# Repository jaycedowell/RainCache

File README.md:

# RainCache

## Parts List
 * Arduino Nano ESP32
 * Adafruit Universal USB / DC / Solar Lithium Ion/Polymer charger - bq24074
 * Adafruit MAX17048 LiPoly / LiIon Fuel Gauge and Battery Monitor
 * Adafruit VL53L1X Time of Flight Distance Sensor - ~30 to 4000mm
 * Xain-USA: 3.7V 4400mAh, Li-ion rechargeable Battery Pack
 * Solar panel charger, 3W 6V
 * Norwesco 44405 1175 gallon Low Profile Underground Water Tank - x4
 * 3" PVC cap
 * 3" to 1 1/2" PVC reducer

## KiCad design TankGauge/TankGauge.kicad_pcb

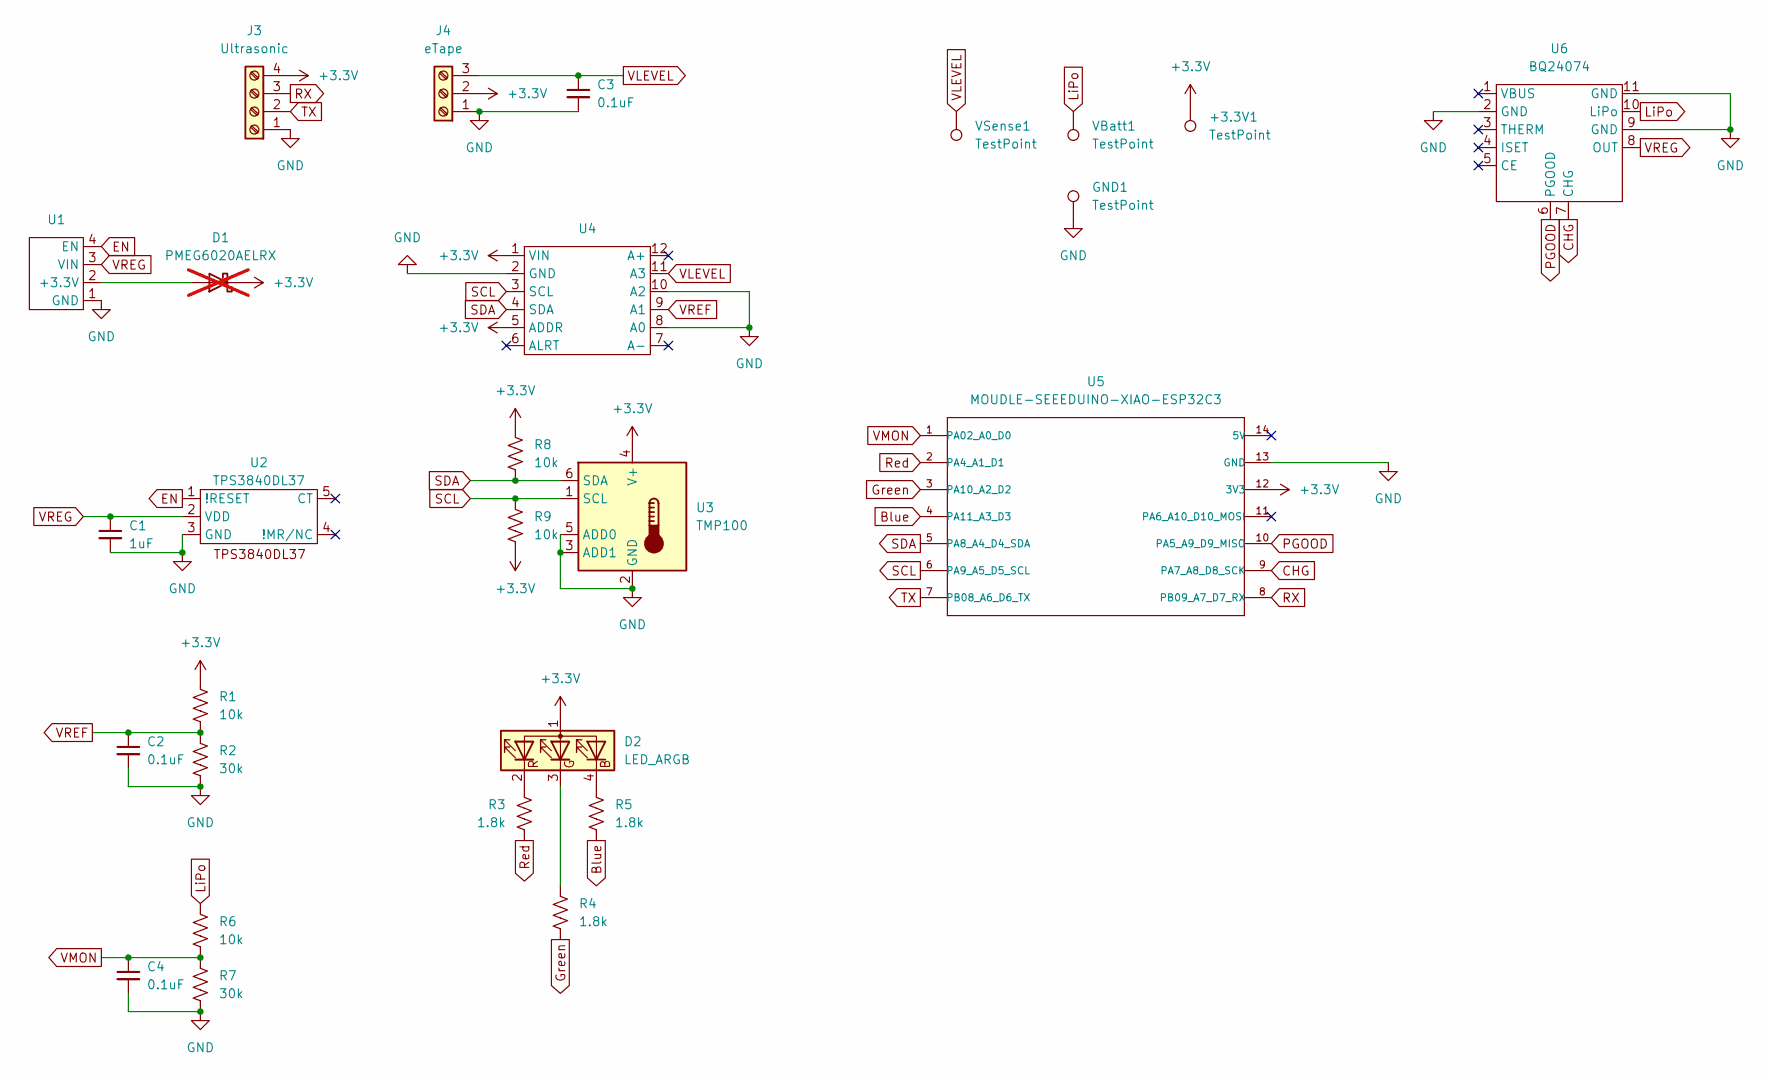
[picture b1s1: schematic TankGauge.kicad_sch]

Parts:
+3.3V1: TestPoint; TestPoint_Pad_D2.0mm
C1: 1uF; C_0805_2012Metric_Pad1.18x1.45mm_HandSolder
C2, C3, C4: 0.1uF; C_0805_2012Metric_Pad1.18x1.45mm_HandSolder
D1: PMEG6020AELRX; Nexperia_CFP3_SOD-123W; not fitted
D2: LED_ARGB; LED_Kingbright_AAA3528ESGCT
GND1: TestPoint; TestPoint_Pad_D2.0mm
J3: Ultrasonic; PinHeader_1x04_P2.54mm_Vertical
J4: eTape; PinHeader_1x03_P2.54mm_Vertical
R1, R6, R8, R9: 10k; R_0805_2012Metric_Pad1.20x1.40mm_HandSolder
R2, R7: 30k; R_0805_2012Metric_Pad1.20x1.40mm_HandSolder
R3, R4, R5: 1.8k; R_0805_2012Metric_Pad1.20x1.40mm_HandSolder
U1: TLV62569; TLV62569 Breakout Board
U2: TPS3840DL37; SOT-23-5_HandSoldering
U3: TMP100; SOT-23-6
U4: ADS1115 Breakout Board
U5: MOUDLE-SEEEDUINO-XIAO-ESP32C3; XIAO-ESP32C3
U6: BQ24074; PinHeader_1x11_P2.54mm_Vertical
VBatt1: TestPoint; TestPoint_Pad_D2.0mm
VSense1: TestPoint; TestPoint_Pad_D2.0mm

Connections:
+3.3V: +3.3V1.1, D1.1 (K), D2.1 (A), J3.4, J4.2, R1.1, R8.1, R9.2, U3.4 (V+), U4.1 (VIN), U4.5 (ADDR), U5.12 (3V3)
Blue: R5.2, U5.4 (PA11_A3_D3)
CHG: U5.9 (PA7_A8_D8_SCK), U6.7 (CHG)
EN: U1.4 (EN), U2.1 (!RESET)
GND: C1.2, C2.2, C3.2, C4.2, GND1.1, J3.1, J4.1, R2.2, R7.2, U1.1 (GND), U2.3 (GND), U3.2 (GND), U3.3 (ADD1), U3.5 (ADD0), U4.2 (GND), U4.8 (A0), U4.10 (A2), U5.13 (GND), U6.2 (GND), U6.9 (GND), U6.11 (GND)
Green: R4.2, U5.3 (PA10_A2_D2)
LiPo: R6.1, U6.10 (LiPo), VBatt1.1
unnamed: D1.2 (A), U1.2 (+3.3V)
unnamed: D2.4 (BK), R5.1
unnamed: D2.3 (GK), R4.1
unnamed: D2.2 (RK), R3.1
PGOOD: U5.10 (PA5_A9_D9_MISO), U6.6 (PGOOD)
RX: J3.3, U5.8 (PB09_A7_D7_RX)
Red: R3.2, U5.2 (PA4_A1_D1)
SCL: R9.1, U3.1 (SCL), U4.3 (SCL), U5.6 (PA9_A5_D5_SCL)
SDA: R8.2, U3.6 (SDA), U4.4 (SDA), U5.5 (PA8_A4_D4_SDA)
TX: J3.2, U5.7 (PB08_A6_D6_TX)
VLEVEL: C3.1, J4.3, U4.11 (A3), VSense1.1
VMON: C4.1, R6.2, R7.1, U5.1 (PA02_A0_D0)
VREF: C2.1, R1.2, R2.1, U4.9 (A1)
VREG: C1.1, U1.3 (VIN), U2.2 (VDD), U6.8 (OUT)

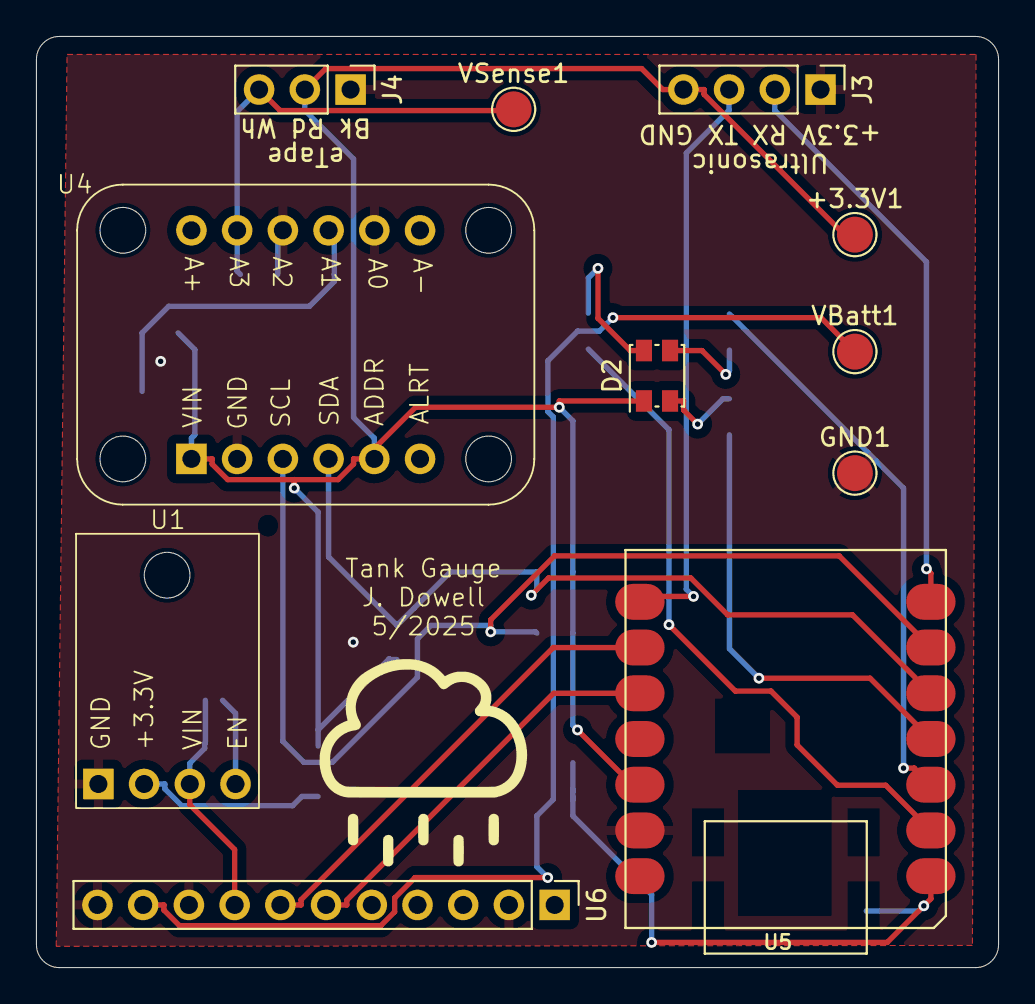
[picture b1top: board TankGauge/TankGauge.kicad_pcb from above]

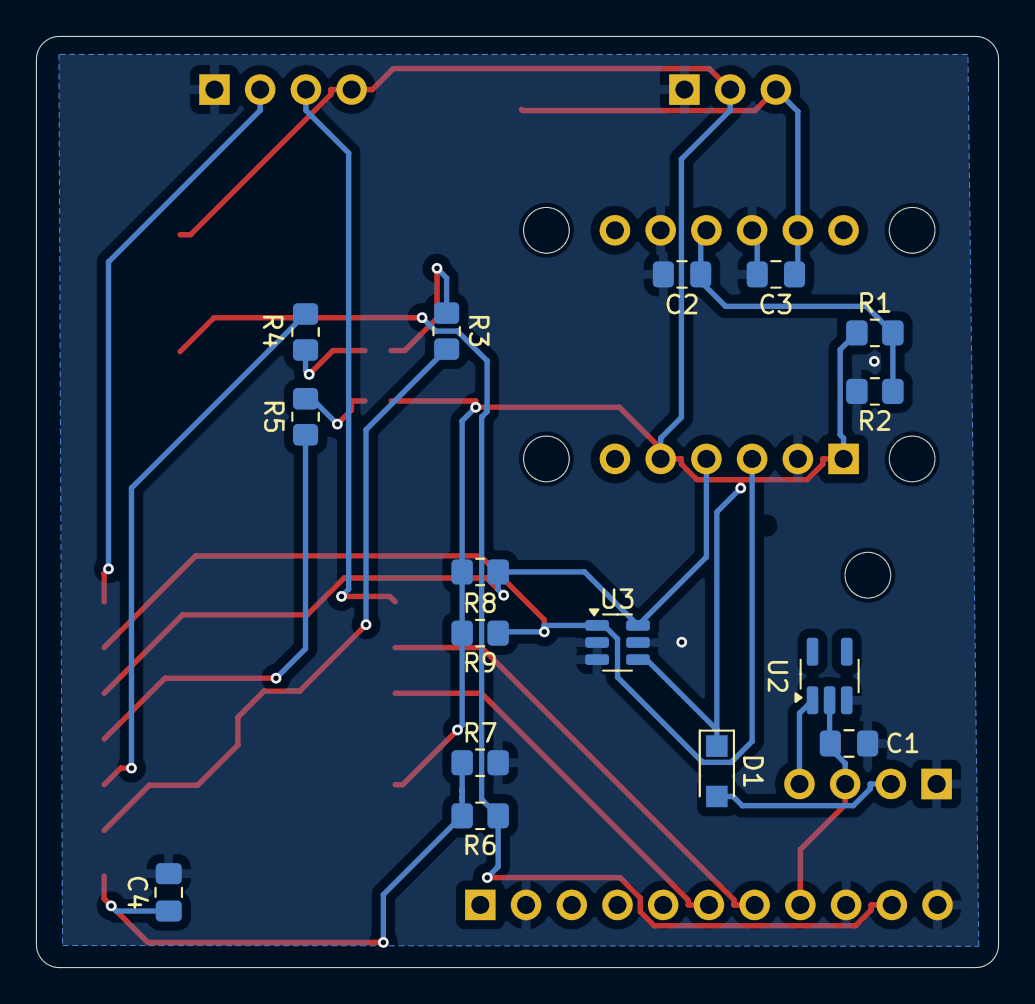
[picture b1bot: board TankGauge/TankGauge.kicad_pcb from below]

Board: 2 copper layers, 53.5 x 51.7 mm, 28 parts (16 on the bottom side), 21 nets.

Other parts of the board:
G1: LOGO; RainCache

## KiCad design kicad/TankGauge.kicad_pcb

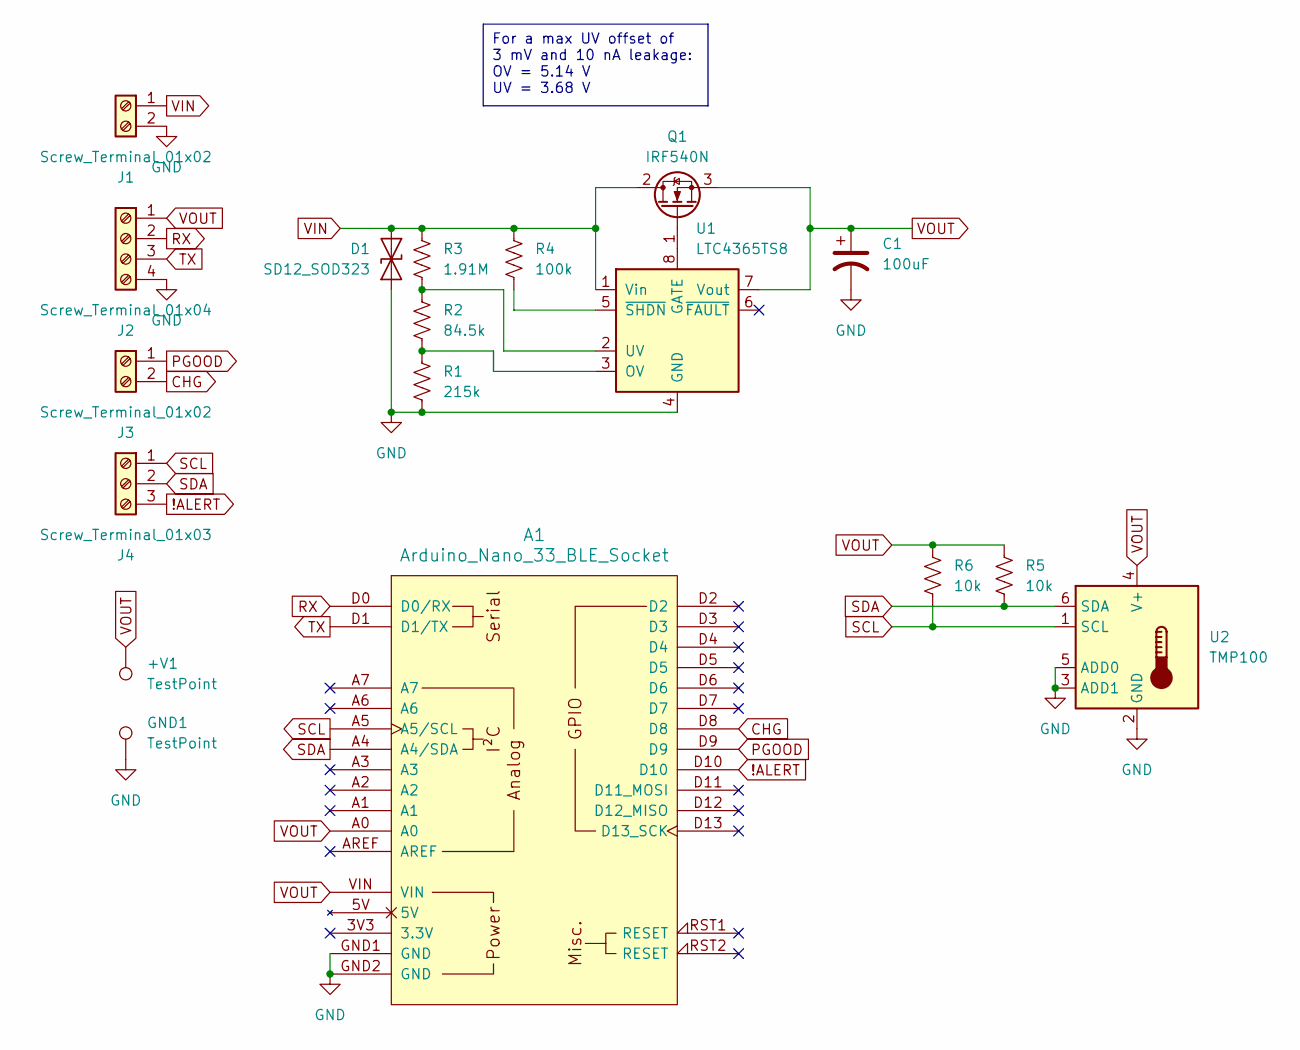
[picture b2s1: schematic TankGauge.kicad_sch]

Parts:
+V1: TestPoint; TestPoint_Pad_D2.0mm
A1: Arduino_Nano_33_BLE_Socket; Arduino_Nano_Every_Socket
C1: 100uF; CP_Radial_D6.3mm_P2.50mm
D1: SD12_SOD323; D_SOD-323
GND1: TestPoint; TestPoint_Pad_D2.0mm
J1, J3: Screw_Terminal_01x02; PinHeader_1x02_P2.54mm_Vertical
J2: Screw_Terminal_01x04; PinHeader_1x04_P2.54mm_Vertical
J4: Screw_Terminal_01x03; PinHeader_1x03_P2.54mm_Vertical
Q1: IRF540N; TO-220-3_Vertical
R1: 215k; R_0805_2012Metric_Pad1.20x1.40mm_HandSolder
R2: 84.5k; R_0805_2012Metric_Pad1.20x1.40mm_HandSolder
R3: 1.91M; R_0805_2012Metric_Pad1.20x1.40mm_HandSolder
R4: 100k; R_0805_2012Metric_Pad1.20x1.40mm_HandSolder
R5, R6: 10k; R_0805_2012Metric_Pad1.20x1.40mm_HandSolder
U1: LTC4365TS8; TSOT-23-8
U2: TMP100; SOT-23-6

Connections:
!ALERT: A1.D10, J4.3
CHG: A1.D8, J3.2
GND: A1.GND1 (GND), A1.GND2 (GND), C1.2, D1.1 (A1), GND1.1, J1.2, J2.4, R1.2, U1.4 (GND), U2.2 (GND), U2.3 (ADD1), U2.5 (ADD0)
unnamed: Q1.1 (G), U1.8 (GATE)
unnamed: R1.1, R2.2, U1.3 (OV)
unnamed: R2.1, R3.2, U1.2 (UV)
unnamed: R4.2, U1.5 (~SHDN)
PGOOD: A1.D9, J3.1
RX: A1.D0 (D0/RX), J2.2
SCL: A1.A5 (A5/SCL), J4.1, R6.2, U2.1 (SCL)
SDA: A1.A4 (A4/SDA), J4.2, R5.2, U2.6 (SDA)
TX: A1.D1 (D1/TX), J2.3
VIN: D1.2 (A2), J1.1, Q1.2 (D), R3.1, R4.1, U1.1 (Vin)
VOUT: +V1.1, A1.A0, A1.VIN, C1.1, J2.1, Q1.3 (S), R5.1, R6.1, U1.7 (Vout), U2.4 (V+)

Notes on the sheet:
For a max UV offset of 3 mV and 10 nA leakage: OV = 5.14 V UV = 3.68 V

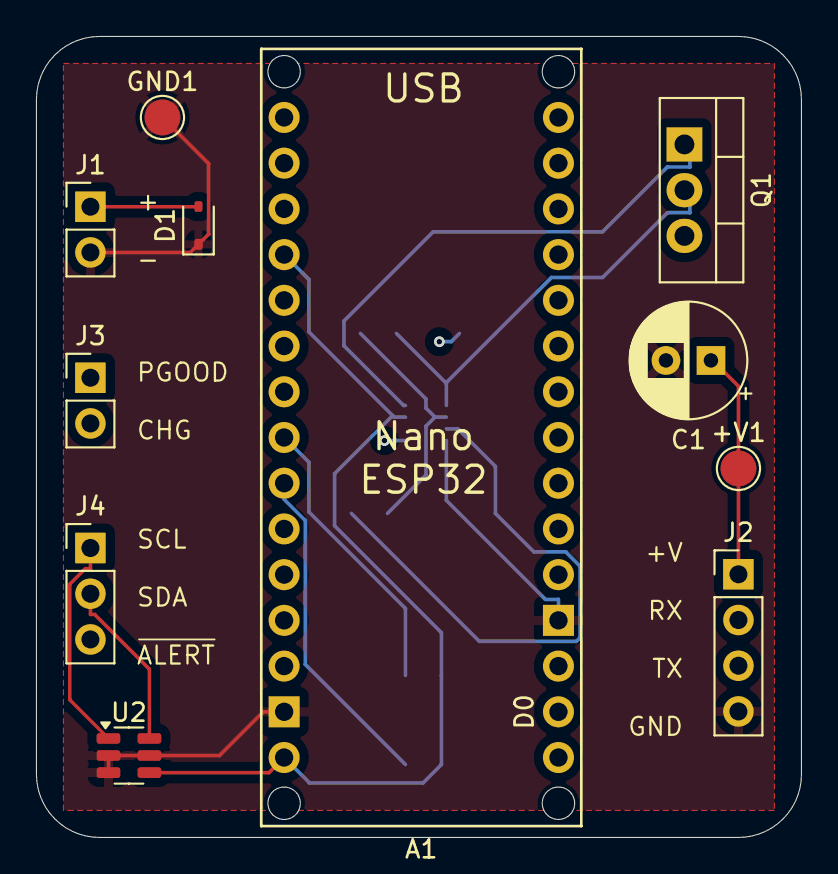
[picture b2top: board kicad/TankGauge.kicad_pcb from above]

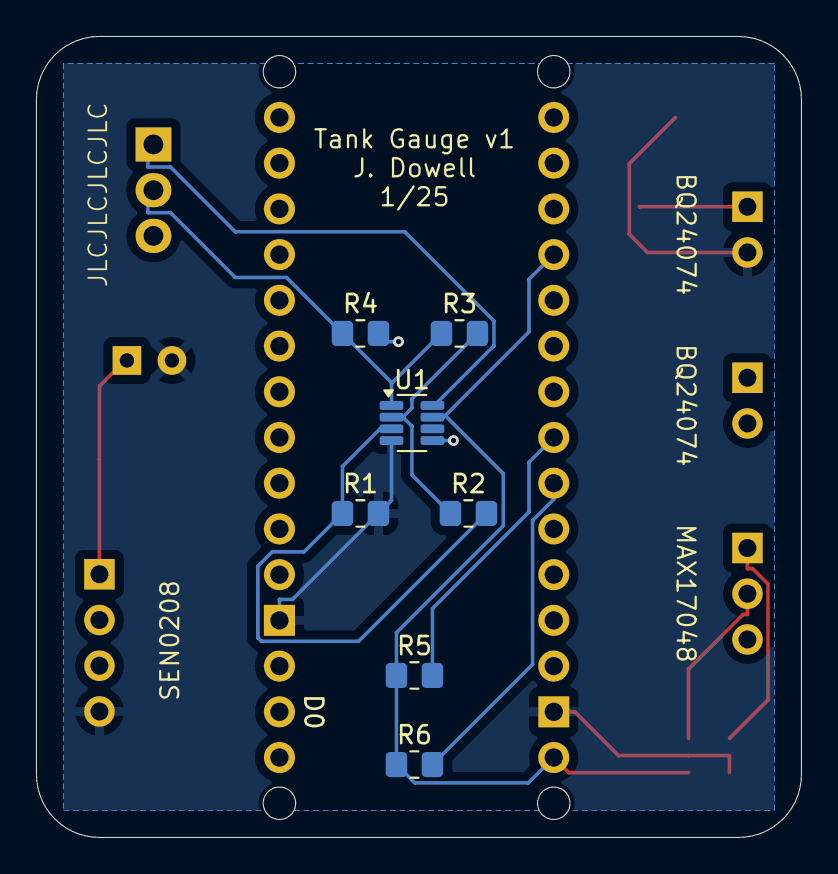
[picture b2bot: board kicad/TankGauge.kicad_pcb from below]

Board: 4 copper layers, 42.5 x 44.5 mm, 18 parts (7 on the bottom side), 14 nets.

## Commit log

2024-09-06 Initial version.
2024-09-06 Reorg
2024-09-06 Add the time-of-flight based version as well.
2024-09-06 Add a parts list.
2024-09-06 Add the time-of-light sensor board.
2025-03-01 Add support for the new PCB that includes a TMP100 temperature sensor. Plus, many cleanups to improve stability.
2025-03-01 Add PCB schematics.
2025-03-01 Added a voltage divider to address #1.
2025-03-02 Fixed an infinite loop when there is a problem reading from the distance sensor. Also, better failure diagnostics and periodic time syncs.
2025-06-14 Use the eTape and a ADS1115 for better results.
2025-06-16 Use more macros and add a readout of the reference voltage.
2025-06-16 DNP D1 since it has too much voltage drop across it.
2025-06-18 Change voltage divider ratio on the battery monitor.
2025-06-18 Update for new battery voltage divider and fix a few typos.
